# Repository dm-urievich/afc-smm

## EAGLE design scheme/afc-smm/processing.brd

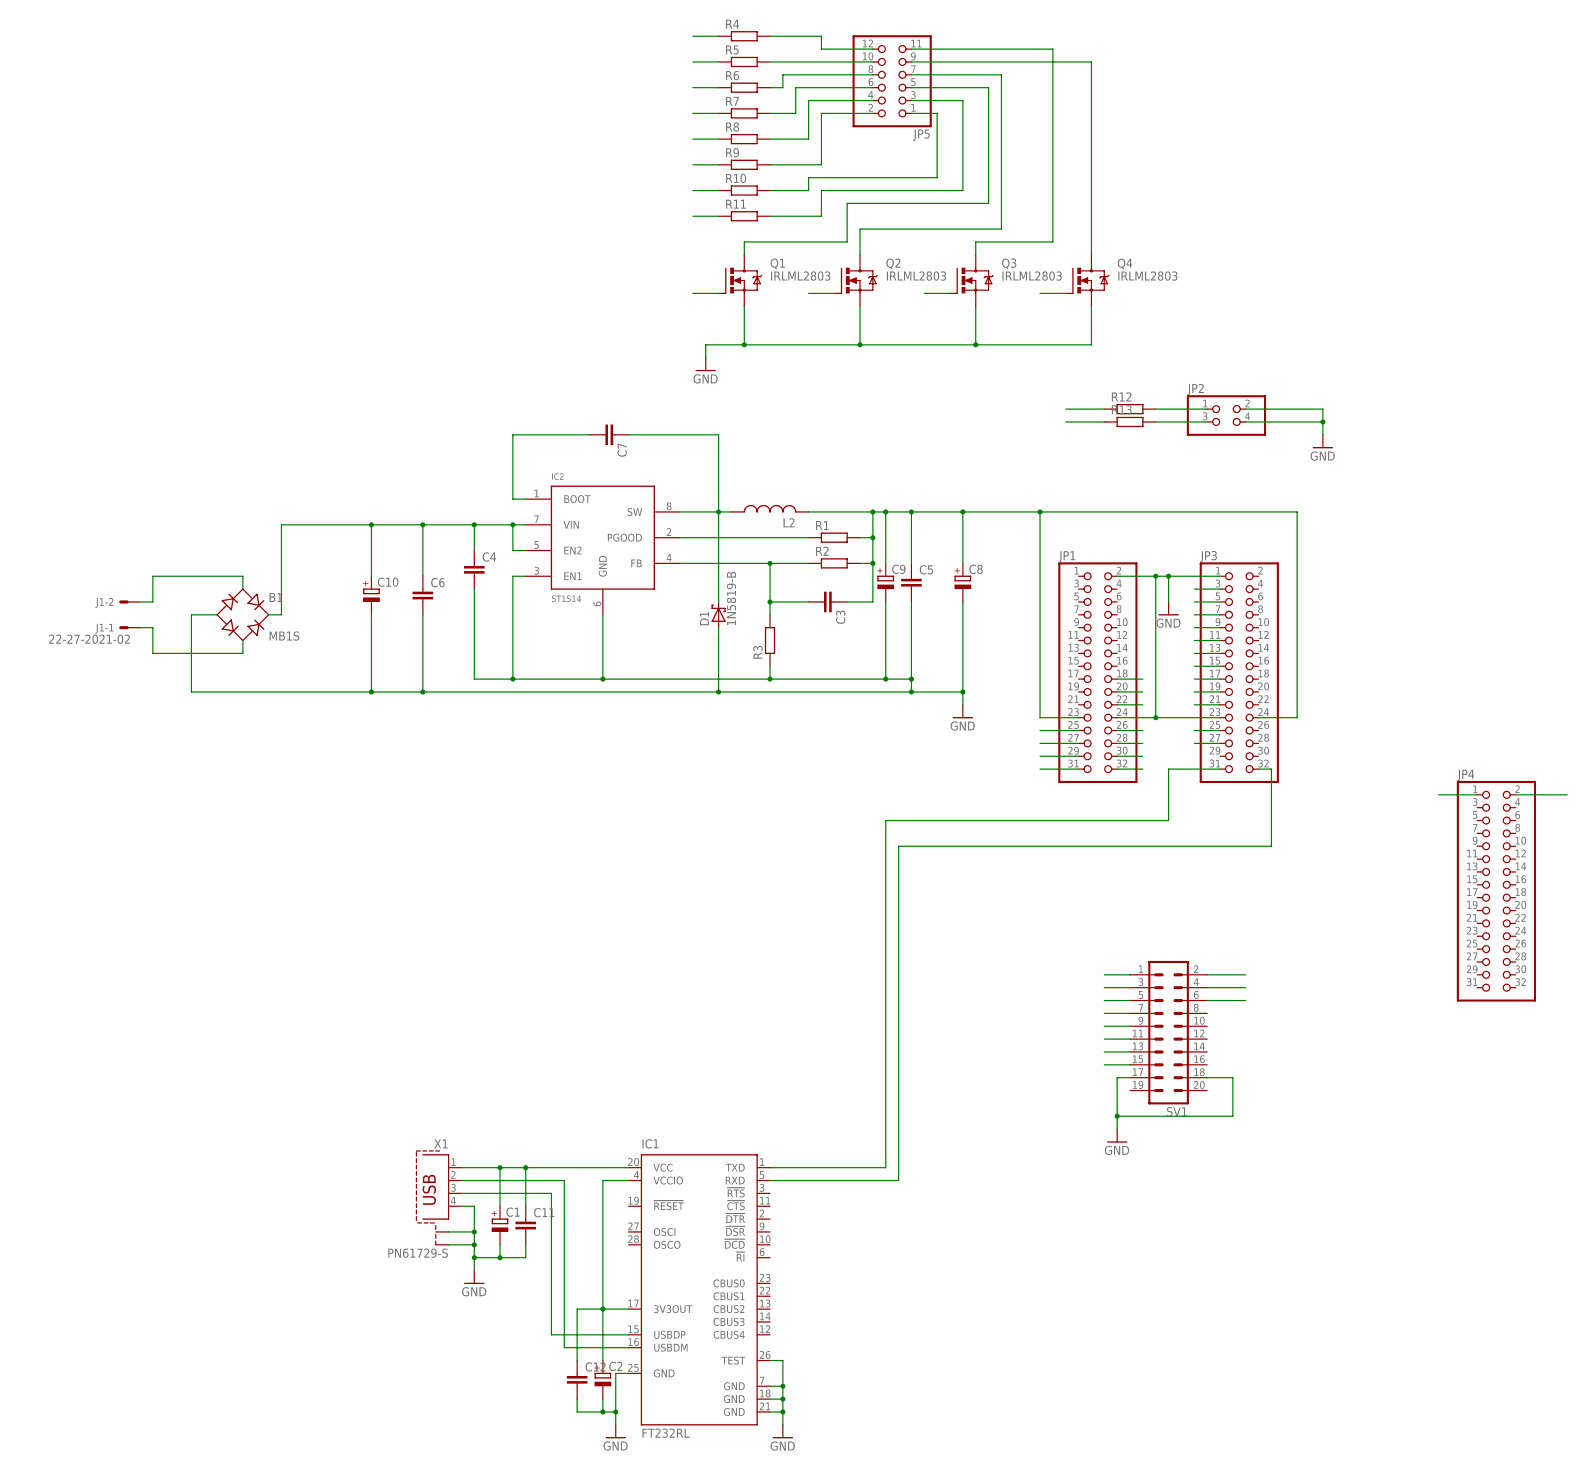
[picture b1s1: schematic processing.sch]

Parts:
B1: MB1S; SOIC-4
C1, C2: CPOL-EUE2.5-5; E2,5-5
C3, C4, C5, C6, C7: C-EUC0805; C0805
C8: CPOL-EUE2.5-6; E2,5-6
C9: CPOL-EUSMCB; SMC_B
C10: CPOL-EUE2.5-7; E2,5-7
C11, C12: C-EUC0603; C0603
D1: 1N5819-B; DO41-7.6
IC1: FT232RL; SSOP28
IC2: ST1S14; SO8
J1: 22-27-2021-02; 6410-02
JP1, JP3, JP4: PINHD-2X16M; 2X16M
JP2: PINHD-2X2; 2X02
JP5: PINHD-2X6; 2X06
L2: L-USWE-TPC; POWER-CHOKE_WE-TPC
Q1, Q2, Q3, Q4: IRLML2803; SOT23
R1, R2, R3: R-EU_R0805; R0805
R4, R5, R6, R7, R8, R9, R10, R11, R12, R13: R-EU_R0603; R0603
SV1: MA10-2W
X1: PN61729-S

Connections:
GND: B1.-, C1.-, C2.-, C4.2, C5.2, C6.2, C8.-, C9.-, C10.-, C11.2, C12.2, D1.A, IC1.7 (GND), IC1.18 (GND), IC1.21 (GND), IC1.25 (GND), IC1.26 (TEST), IC2.3 (EN1), IC2.6 (GND), JP1.2, JP1.24, JP2.2, JP2.4, JP3.1, JP3.23, Q1.2 (S), Q2.2 (S), Q3.2 (S), Q4.2 (S), R3.1, SV1.17, SV1.18, X1.4, X1.S1, X1.S2
L1: JP3.17, R4.1
L2: JP3.15, R5.1
L3: JP3.13, R6.1
L4: JP3.11, R7.1
L5: JP3.9, R8.1
L6: JP3.7, R9.1
L7: JP3.5, R10.1
L8: JP3.3, R11.1
LED1: JP4.1, R12.1
LED2: JP4.2, R13.1
unnamed: IC1.16 (USBDM), X1.2
unnamed: IC1.15 (USBDP), X1.3
unnamed: C1.+, C11.1, IC1.20 (VCC), X1.1
unnamed: IC1.5 (RXD), JP3.32
unnamed: JP2.1, R12.2
unnamed: B1.+, C4.1, C6.1, C10.+, IC2.5 (EN2), IC2.7 (VIN)
unnamed: C7.2, IC2.1 (BOOT)
unnamed: C7.1, D1.C, IC2.8 (SW), L2.1
unnamed: IC2.2 (PGOOD), R1.1
unnamed: C3.2, IC2.4 (FB), R2.1, R3.2
unnamed: C3.1, C5.1, C8.+, C9.+, JP1.23, JP3.24, L2.2, R1.2, R2.2
unnamed: B1.~2 (AC2), J1.1
unnamed: C2.+, C12.1, IC1.4 (VCCIO), IC1.17 (3V3OUT)
unnamed: JP5.12, R4.2
unnamed: JP5.10, R5.2
unnamed: JP5.8, R6.2
unnamed: JP5.6, R7.2
unnamed: JP5.4, R8.2
unnamed: JP5.2, R9.2
unnamed: JP5.9, Q4.3 (D)
unnamed: JP5.11, Q3.3 (D)
unnamed: JP5.7, Q2.3 (D)
unnamed: JP5.5, Q1.3 (D)
unnamed: JP5.3, R11.2
unnamed: JP5.1, R10.2
unnamed: B1.~1 (AC1), J1.2
unnamed: IC1.1 (TXD), JP3.31
unnamed: JP2.3, R13.2
Q1: JP3.27, Q1.1 (G)
Q2: JP3.25, Q2.1 (G)
Q3: JP3.19, Q3.1 (G)
Q4: JP3.21, Q4.1 (G)
R1: JP1.18, SV1.6
R2: JP1.20, SV1.4
R3: JP1.22, SV1.2
R4: JP1.26, SV1.1
R5: JP1.28, SV1.3
R6: JP1.30, SV1.5
R7: JP1.32, SV1.7
R8: JP1.31, SV1.9
R9: JP1.29, SV1.11
R10: JP1.27, SV1.13
R11: JP1.25, SV1.15

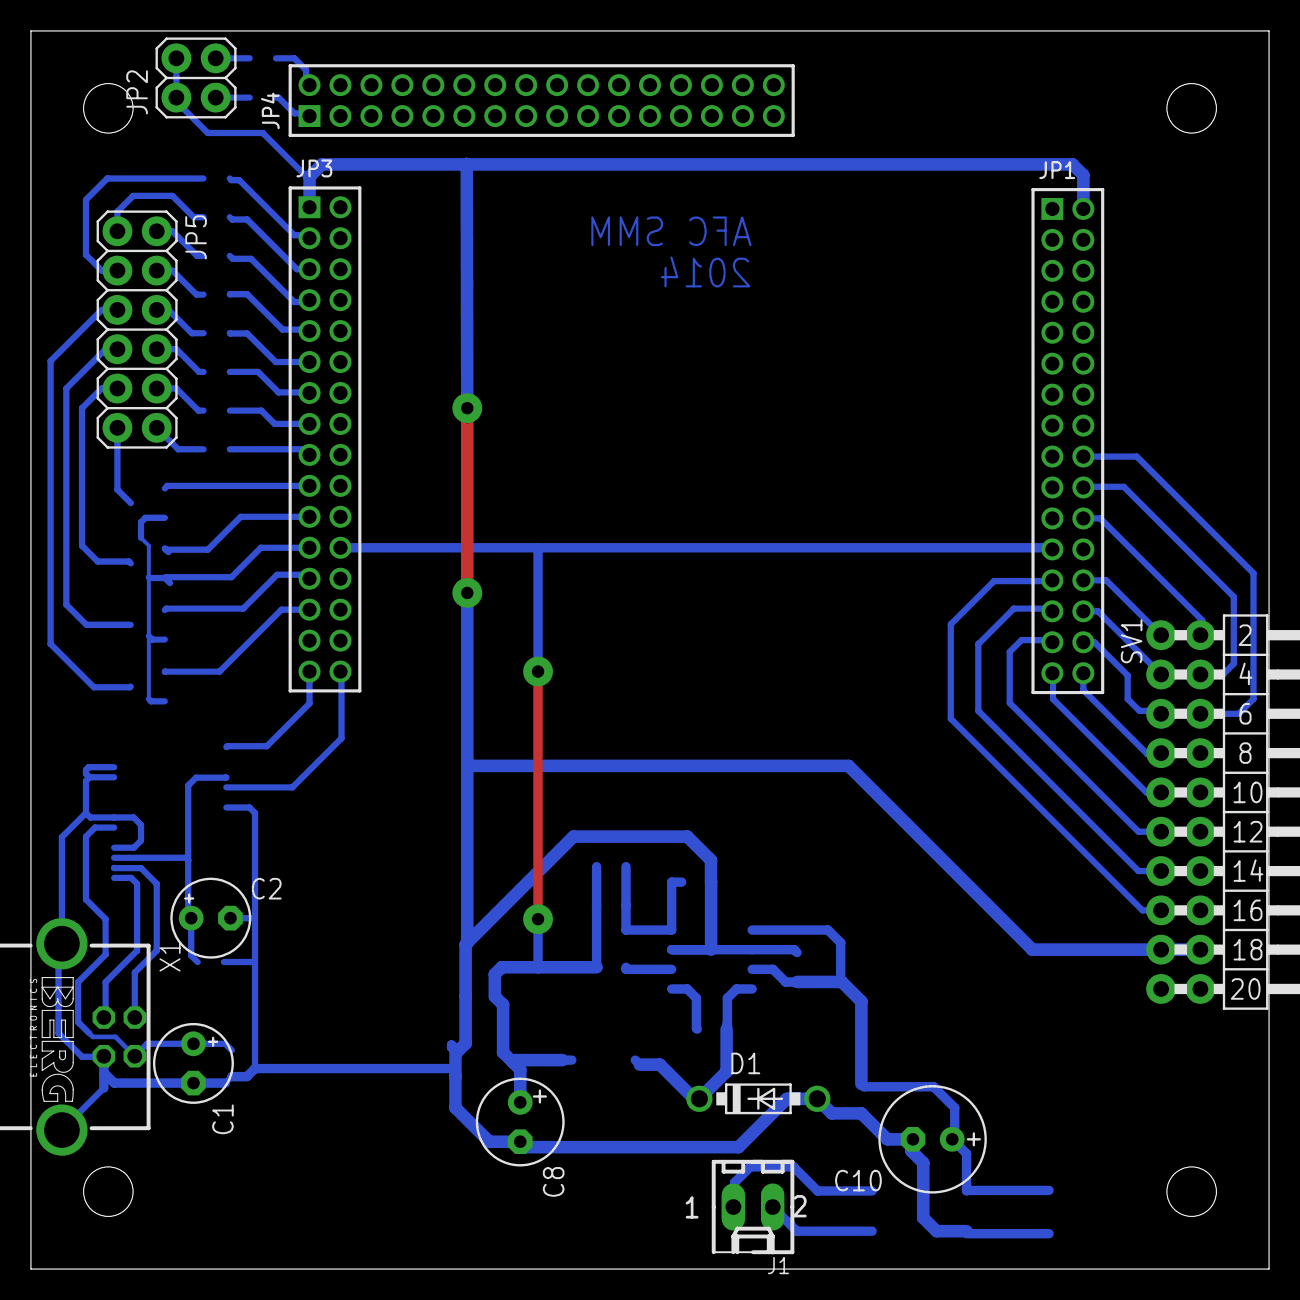
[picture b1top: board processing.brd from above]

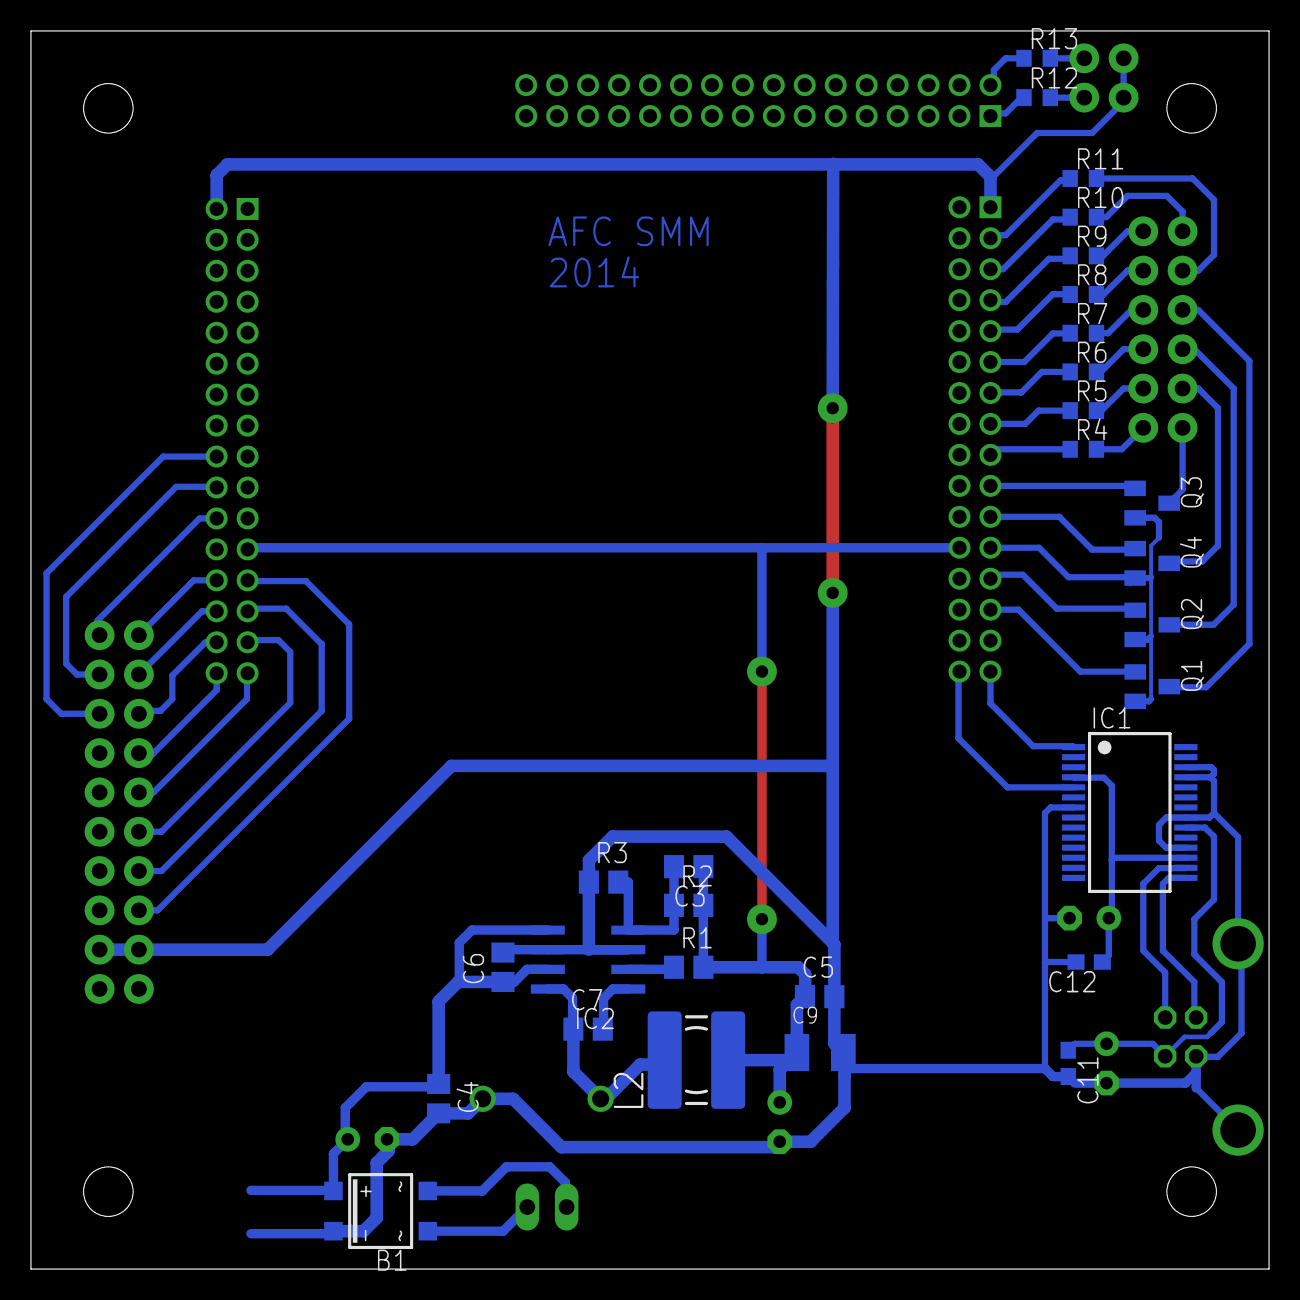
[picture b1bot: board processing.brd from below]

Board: 2 copper layers, 80.0 x 80.0 mm, 42 parts (29 on the bottom side), 54 nets.

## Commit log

2014-06-29 many, work with PID, add scripts for controlling, add new board
